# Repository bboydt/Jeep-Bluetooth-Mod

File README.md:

# Jeep Bluetooth Mod

## About
When I started driving, I wanted Bluetooth in my 2004 Jeep Grand Cherokee. Several years later, I finally got around to building a Bluetooth mod. My radio has a plug for a cd changer, so I used an Arduino and a Bluetooth module to make a pseudo cd changer. It took me about a month, however I procrastinated a lot. [Here's a video of the prototype working (ignore the awful music)](https://youtu.be/_DS7fCqb5ws).

## Useful Info

 - The arduino prototype code is in Jeep/ and the ATtiny version's code is in src/
 - My radio model is p05064354aj.
 - I'm using an Arduino UNO and a XS-3868 Bluetooth module
 - Chrysler radios, made before 2004, use the car’s internal PCI bus for communication with other accessories (i.e. a cd changer). It’s a good idea to be careful when writing to this bus because you could damage your car.
 - My car uses the J1850 VPW protocol.
 - Some good vocabulary to know for this protocol:
    - **Frame** : a packet of data
    - **Cyclical Redundancy Check (CRC)** : it’s a checksum
 - I used two optocouplers to communicate on the bus without frying my Arduino. Also, I put some LEDs on the optocouplers' outputs which was useful for debugging.

## Useful Links

 - [This has a lot of information on what to send to the radio to trick it into thinking you’re a cd changer.](https://www.mictronics.de/projects/cdc-protocols/#ChryslerJeep)
 - [This has good info on the J1850 protocol.](http://www.interfacebus.com/Automotive_SAE_J1850_Bus.html)
 - [A more technical document on J1850.](http://citeseerx.ist.psu.edu/viewdoc/download?doi=10.1.1.506.6682&rep=rep1&type=pdf)
 - [This guy’s project uses the same protocol so it was helpful.](https://github.com/connorwm/J1850VPW)
 - [Radio Pinout (there are also other radio pinouts here)](https://www.tehnomagazin.com/Auto-radio-car-connector/CHRYSLER-Car-Radio-Wiring-Connector.htm)

## Todo

 - Finish converting from the Arduino prototype to the ATtiny version
   - CRC check (Frame Creation in general)
   - Proper Responses to the radio
 - In the current configuration, the relay is unreliable so that needs to be fixed

----

*Benjamin Thomas - boydbt48@gmail.com - 2019*

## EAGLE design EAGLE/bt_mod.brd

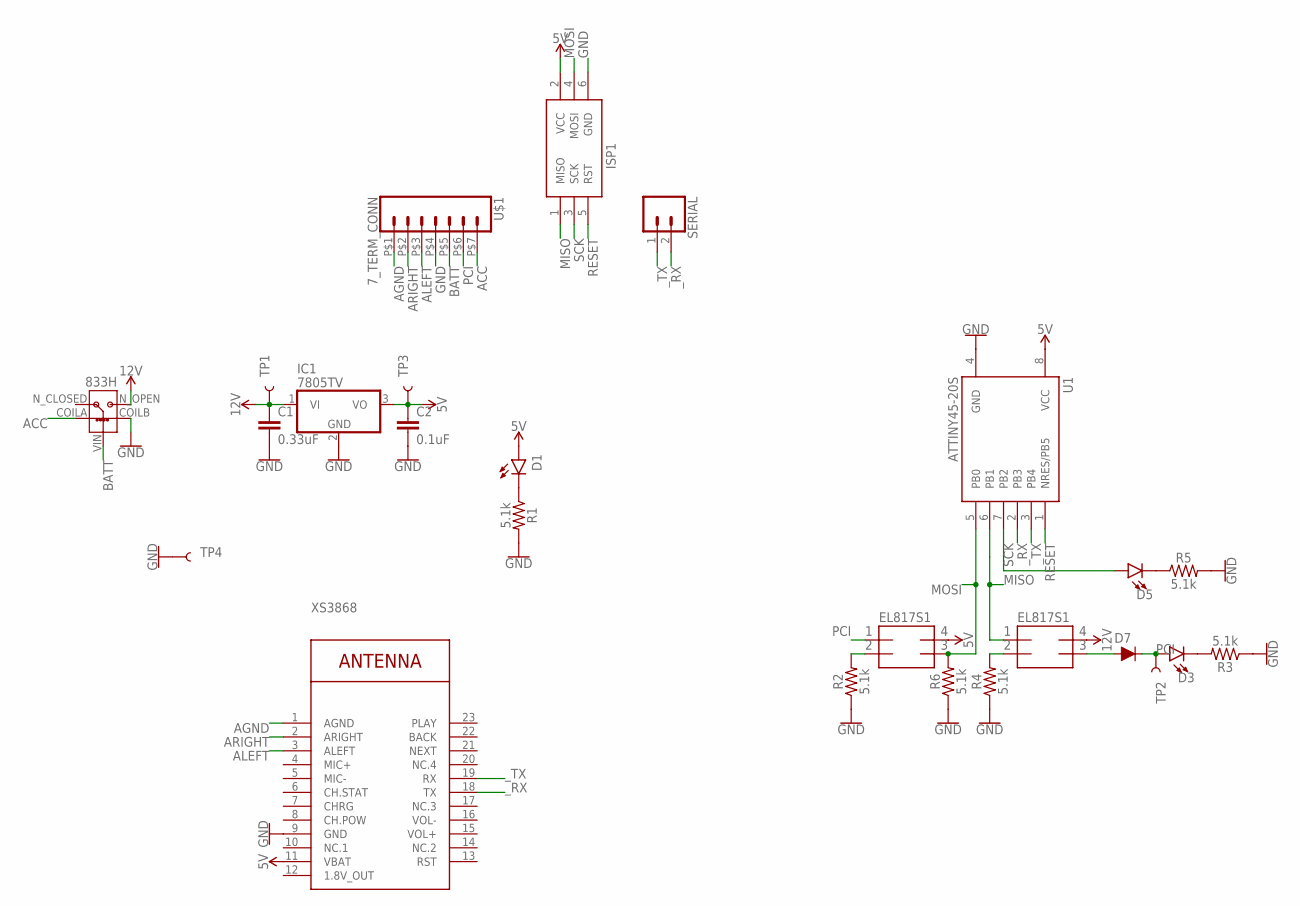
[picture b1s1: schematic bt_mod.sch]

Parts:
1: 833H-1C-C-12VDC
C1: 0.33uF; 0603
C2: 0.1uF; 0603
D1, D3, D5: LED0603; LED-0603
D7: 250mA/100V; SOD-323
IC1: 7805TV; TO220V
INPUT: EL3H7-G; SMD-4
ISP1: AVRISP-6; AVRISP
OUTPUT: EL3H7-G; SMD-4
R1, R2, R3, R4, R5, R6: 5.1k; 0603
SERIAL: CONN_02; 1X02
TP1, TP2, TP3, TP4: TEST-POINT3X5; PAD.03X.05
U1: ATTINY45-20S; SOIC8_EIAJ_208MIL
U$1: 7_TERM_CONN; 7_TERMINALS
XS3868: WIRELESS-BLUETOOTH-XS3868

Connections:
1.8V_OUT: XS3868.12 (1.8V_OUT)
5V: C2.1, D1.A, IC1.3 (VO), INPUT.P$4, ISP1.2 (VCC), TP3.P$1, U1.8 (VCC), XS3868.11 (VBAT)
12V: 1.N_OPEN, C1.1, IC1.1 (VI), OUTPUT.P$4, TP1.P$1
ACC: 1.COILA, U$1.P$7 (7)
AGND: U$1.P$1 (1), XS3868.1 (AGND)
ALEFT: U$1.P$3 (3), XS3868.3 (ALEFT)
ARIGHT: U$1.P$2 (2), XS3868.2 (ARIGHT)
BATT: 1.VIN, U$1.P$5 (5)
GND: 1.COILB, C1.2, C2.2, IC1.2 (GND), ISP1.6 (GND), R1.2, R2.1, R3.1, R4.1, R5.2, R6.1, TP4.P$1, U1.4 (GND), U$1.P$4 (4), XS3868.9 (GND)
MISO: ISP1.1 (MISO), OUTPUT.P$1, U1.6 (PB1)
MOSI: INPUT.P$3, ISP1.4 (MOSI), R6.2, U1.5 (PB0)
unnamed: D1.C, R1.1
unnamed: INPUT.P$2, R2.2
unnamed: OUTPUT.P$2, R4.2
unnamed: D5.C, R5.1
unnamed: D3.C, R3.2
unnamed: D7.A, OUTPUT.P$3
PCI: D3.A, D7.C, INPUT.P$1, TP2.P$1, U$1.P$6 (6)
RESET: ISP1.5 (RST), U1.1 (NRES/PB5)
RST: XS3868.13 (RST)
SCK: D5.A, ISP1.3 (SCK), U1.7 (PB2)
_RX: SERIAL.2, U1.2 (PB3), XS3868.18 (TX)
_TX: SERIAL.1, U1.3 (PB4), XS3868.19 (RX)

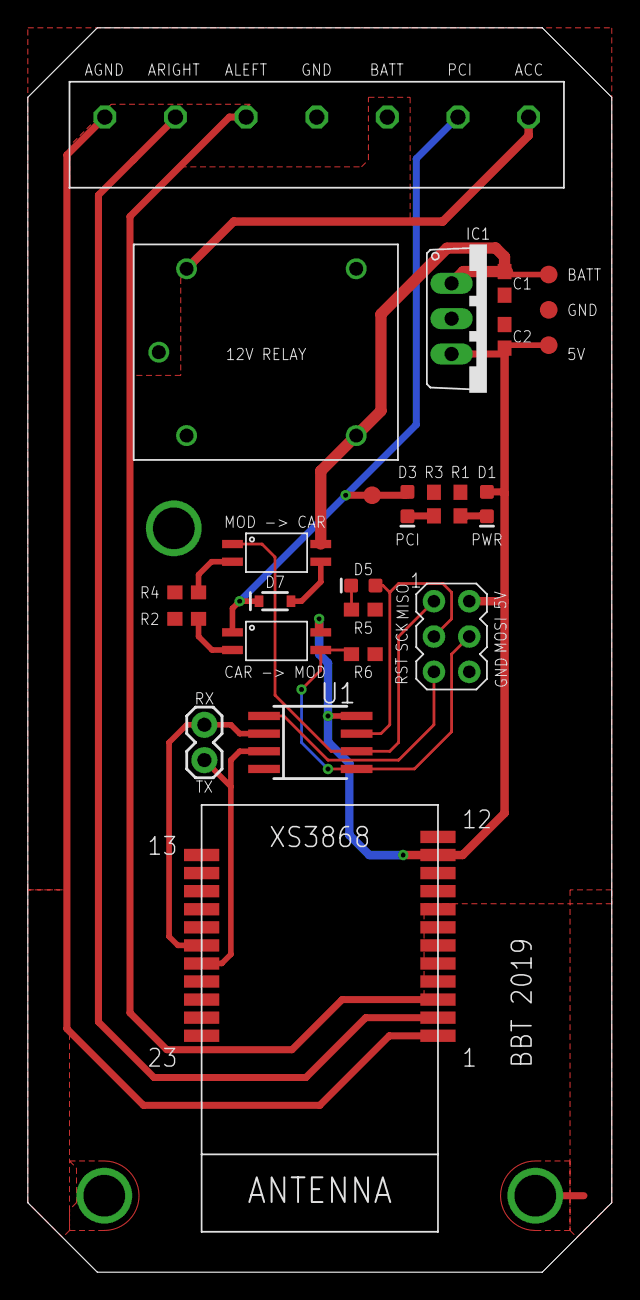
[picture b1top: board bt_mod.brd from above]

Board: 2 copper layers, 42.0 x 89.5 mm, 25 parts (0 on the bottom side), 21 nets.

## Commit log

2020-02-05 Added PCB Desgin
2020-02-05 intial check in
    AVR Progamming Batch Files

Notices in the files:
parts and their libraries:
SparkFun-Capacitors: Licensing: Creative Commons ShareAlike 4.0 International - https://creativecommons.org/licenses/by-sa/4.0
xs3868: Released under the Creative Commons Attribution 4.0 International License: http://creativecommons.org/licenses/by/4.0
